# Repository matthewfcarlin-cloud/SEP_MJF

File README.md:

# RECO

**A smart tape and app that helps people recovering from an injury get back to their lives sooner, with fewer setbacks. It tracks the injured joint every day, shows their progress and what comes before their pain, and gives their PT the full picture between visits.**

A PT sees you for 1 to 3 hours a week. RECO covers the other 160+.

- **Track:** the tape records how the joint moves and how much it's used through daily life.
- **Log:** press the button on the device when something hurts.
- **Learn:** RECO finds what comes before your pain and learns your line.
- **Adapt:** your progress, plan and warnings update from what you actually did.
- **Share:** your PT gets a data-driven report before each appointment.

The vision covers knee, shoulder and elbow injuries, with or without a PT. The first version starts with the knee. RECO was first called Kinn, so the code still lives under `kinn/`.

## Start here

- **Vision:** [`kinn/docs/vision.md`](kinn/docs/vision.md) is the source of truth for what RECO is, who it's for, and what's still open.
- **Decisions:** [`kinn/docs/decisions.md`](kinn/docs/decisions.md) is the running log of what was decided and why.
- **History:** [`kinn/CONTEXT.md`](kinn/CONTEXT.md) covers how the product got here, along with brand, site and market notes.

## In this repo

- **App:** [`kinn/app/`](kinn/app/) is the Expo app and the `@reco/core` logic package. Details are in [`feature-spec.md`](kinn/docs/feature-spec.md) (written before the current vision), [`architecture.md`](kinn/docs/architecture.md), [`scoring-methods.md`](kinn/docs/scoring-methods.md) and [`backend.md`](kinn/docs/backend.md).
- **Hardware:** [`kinn/firmware/`](kinn/firmware/) and [`kinn/hardware/`](kinn/hardware/) hold the prototype tape firmware and coin PCB. [`kinn/cad/`](kinn/cad/) holds the CAD.
- **Website and waitlist:** [`kinn/site/`](kinn/site/) is the static site and a small Express API, deployed on Vercel. Setup is in its README.
- **Renders and video:** [`kinn/renders/`](kinn/renders/), [`kinn/video/`](kinn/video/) and the scene scripts in [`kinn/blender/`](kinn/blender/).
- **Archive:** [`kinn/archive/`](kinn/archive/) holds earlier concepts and demos, including the Poise posture strip and the hackathon learning demo.

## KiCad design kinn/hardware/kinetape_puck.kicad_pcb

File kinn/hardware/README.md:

# KineTape puck — PCB (rev A)

A 25.4 mm (1 in) round, 4-layer board that snaps onto the tape: ESP32 + printed BLE antenna,
capacitive touch button, status LED, and four spring contacts on the bottom that reach the battery
and pressure sensor built into the tape.

| | |
|---|---|
|  |  |

**Status:** schematic ERC-clean; board fully routed, **0 DRC violations / 0 unconnected / 0 schematic-parity
errors** (KiCad 10.0.7, all severities). **Not yet fabricated or RF-tested** — see [Before you order](#before-you-order).

## What's on it

| Block | Parts | Notes |
|---|---|---|
| MCU | U1 ESP32-PICO-V3-02 (LGA-48, 7×7 mm) | Classic ESP32 + 8 MB flash + 2 MB PSRAM + crystal in one package, so the existing `esp32dev` firmware runs. |
| Antenna | AE1 printed inverted-F, R10 + C11/C12 pi network | IFA runs along the top edge (above the ground cut). C11/C12 are **DNP** until tuned. |
| Power | Q1 AO3401A, U2 ME6211 3.3 V LDO, C1/C3 | Battery comes from the tape (J1). Q1 = reverse-polarity protection. ME6211: 500 mA, VIN up to 6 V. |
| Battery sense | R1/R2 1 MΩ divider + C4 → GPIO35 | VBAT/2, ~2 µA drain. |
| Sensor | J3/J4 + R7, R8, R9, C10 | Same divider as the firmware README: 3V3 → sensor → GPIO34 with 10 kΩ to GND (+1 kΩ/100 nF RC filter). |
| Touch | TS1 Ø6.5 mm electrode, R6 470 Ω | Electrode on the top layer under solder mask; no copper under it on inner/bottom layers. |
| LED | LED1 green 0603, R5 470 Ω → GPIO2 | Same pin as the firmware. |
| ESD | D1–D3 (0402) on every tape contact | The contacts touch the tape and skin. |

### Tape contacts (bottom side, Harwin P70-1000045R SMT spring pins)

| Contact | Net | Position (from centre, top view) |
|---|---|---|
| J1 | VBAT in (3.0–5.5 V) | (+8.8, +1.5) mm |
| J2 | GND | (+6.5, −7.2) mm |
| J3 | SENS_A (3.3 V via 100 Ω) | (−8.8, +1.5) mm |
| J4 | SENS_B (→ ADC) | (−6.5, −7.2) mm |

The pattern is deliberately asymmetric, so the puck can only mate one way. The tape needs four flat
conductive pads (snaps, conductive fabric or foil) at these positions. Spring free height is 3.5 mm,
working height 2.9 mm.

### GPIO map (firmware)

| GPIO | Function | vs current firmware |
|---|---|---|
| 34 | Sensor ADC (ADC1_CH6) | unchanged |
| 2 | Status LED | unchanged |
| 35 | Battery sense, VBAT/2 (ADC1_CH7) | new; matches the "Future" note in `firmware/README.md` |
| 13 | Touch button (`T4`, `touchRead(13)`) | new |
| 1 / 3 | UART0 TX / RX (programming pads) | unchanged |
| 0 / EN | Boot / reset (programming pads) | — |

### Programming

The 2×3 pad grid on the bottom (Ø1.0 mm, 2.0 mm pitch) is for a pogo-pin jig plus a 3.3 V USB-UART adapter:

```
TP3 TXD  (4.5,-1.0)   TP4 RXD (6.5,-1.0)   TP1 3V3 (8.5,-1.0)
TP5 EN   (4.5,-3.0)   TP6 IO0 (6.5,-3.0)   TP2 GND (8.5,-3.0)
```

There is no auto-reset circuit. To enter the bootloader, hold IO0 to GND and pulse EN to GND, then flash
with `pio run -t upload`. To power the board for flashing, feed VBAT through J1. Back-feeding TP1 (3V3)
works but pushes current into the LDO output.

## Board

- 25.4 mm circle, **4 layers, 1.0 mm** FR-4. F.Cu signals + GND pour; In1 = solid GND plane;
  In2 = +3V3 plane; B.Cu signals + GND pour.
- Rules: 0.15 mm track/space (power 0.25–0.3 mm), vias 0.5/0.3 mm (thermal-pad vias 0.5/0.25 mm),
  all within JLCPCB's standard 4-layer capability.
- RF feed: 0.2 mm trace, pre-routed and locked; ground stitching along the antenna ground edge.
- No copper on any layer above the ground edge (antenna keepout), and none under the touch electrode on the
  inner and bottom layers.

## Before you order

These are the things I could not verify from here. Each one should be checked rather than assumed.

1. **The antenna is untuned and uncertified.** The IFA (19.9 mm arm + stub) is deliberately a bit long,
   so it should resonate low. Plan on a VNA (a NanoVNA is enough): measure S11 at R10, trim the open end
   of the arm, and fit C11/C12 to match 50 Ω. The enclosure and skin will detune it further, so tune it
   inside the enclosure, on an arm. Without tuning, BLE will probably still work at a few metres, but range
   is unknown. A bare chip with your own antenna also means the radio is uncertified (FCC/CE), which is fine
   for a prototype but not for selling it.
2. **ESP32 land pattern.** The LGA-48 footprint is built from Espressif's datasheet (v1.4, Fig. 16:
   0.25 × 0.68 mm lands, 6.73 mm between opposite land centres, 4.5 mm thermal pad with a 4.0 mm
   mask opening). Compare it against Espressif's land-pattern source file before ordering.
3. **Spring-contact pad.** Ø2.4 mm pad for the Ø2.0 mm Harwin P70-1000045R body. Check it against
   Harwin's drawing.
4. **JLCPCB part numbers.** Check stock and Basic/Extended status in the BOM upload. The ESP32
   (C908392), ESD diodes and springs are Extended parts, so each adds a loading fee.
5. **Rotations.** In JLCPCB's placement preview, check pin 1 of U1, the orientation of U2/Q1, and LED1
   polarity.
6. **Double-sided assembly.** J1–J4 are on the bottom. Either pay for both sides, or assemble the top
   only and hand-solder the four springs.
7. **Battery and power budget.** BLE on a classic ESP32 averages roughly 40–100 mA, with peaks around
   130–250 mA. The battery in the tape has to deliver those peaks through the contacts, so contact
   resistance matters. Firmware sleep (see the power notes in `firmware/README.md`) decides battery life
   far more than this board does.

## Regenerating

Everything is generated from [`scripts/design.py`](scripts/design.py) (parts, nets, placement).
Don't hand-edit the `.kicad_*` files and then rerun the scripts, because the scripts overwrite them.
Run with KiCad's Python from `hardware/`:

```bash
"C:/Program Files/KiCad/10.0/bin/python.exe" scripts/build.py    # footprints, schematic, placed board, fanout
"C:/Program Files/KiCad/10.0/bin/python.exe" scripts/route.py    # Freerouting + finishing router + stitching
"C:/Program Files/KiCad/10.0/bin/python.exe" scripts/export.py   # DRC gate, then fab/ outputs
```

`route.py` needs `tools/freerouting.jar` (Freerouting 1.9.0, Java 17; git-ignored). It briefly opens a
Freerouting window. Whatever Freerouting leaves unrouted, the grid router in `scripts/finish.py`
completes. `export.py` refuses to write outputs unless DRC and schematic parity are clean.

| Script | Does |
|---|---|
| `design.py` | The circuit: every part, its LCSC number, pin → net, PCB position |
| `footprints.py` | Custom footprints: ESP32-PICO LGA-48, IFA antenna, touch pad, spring contact |
| `schematic.py` | Writes the `.kicad_sch` (net labels on every pin); KiCad's own netlist export is then checked against `design.py` |
| `build.py` | Board outline, placement, pours, keepouts, locked RF route, power fanout and escape vias |
| `fanout.py` / `finish.py` | Clearance-checked via fanout; grid A* router for leftovers |
| `export.py` | Gerbers + drill zip, JLCPCB BOM/CPL, schematic PDF, STEP |

## Ordering (JLCPCB)

1. Upload `fab/kinetape_puck_gerbers.zip`. Set 4 layers, 1.0 mm, ENIG (recommended for the LGA and the
   spring contacts), and the default impedance-free stackup.
2. PCB Assembly: upload `fab/kinetape_puck_bom.csv` and `fab/kinetape_puck_cpl.csv`, then check the
   placement preview (see item 5 above).
3. Optional: use `fab/kinetape_puck.step` to design the enclosure. It has the antenna at the top edge,
   and the touch electrode should sit under a thin (≤ 1.5 mm) plastic lid.

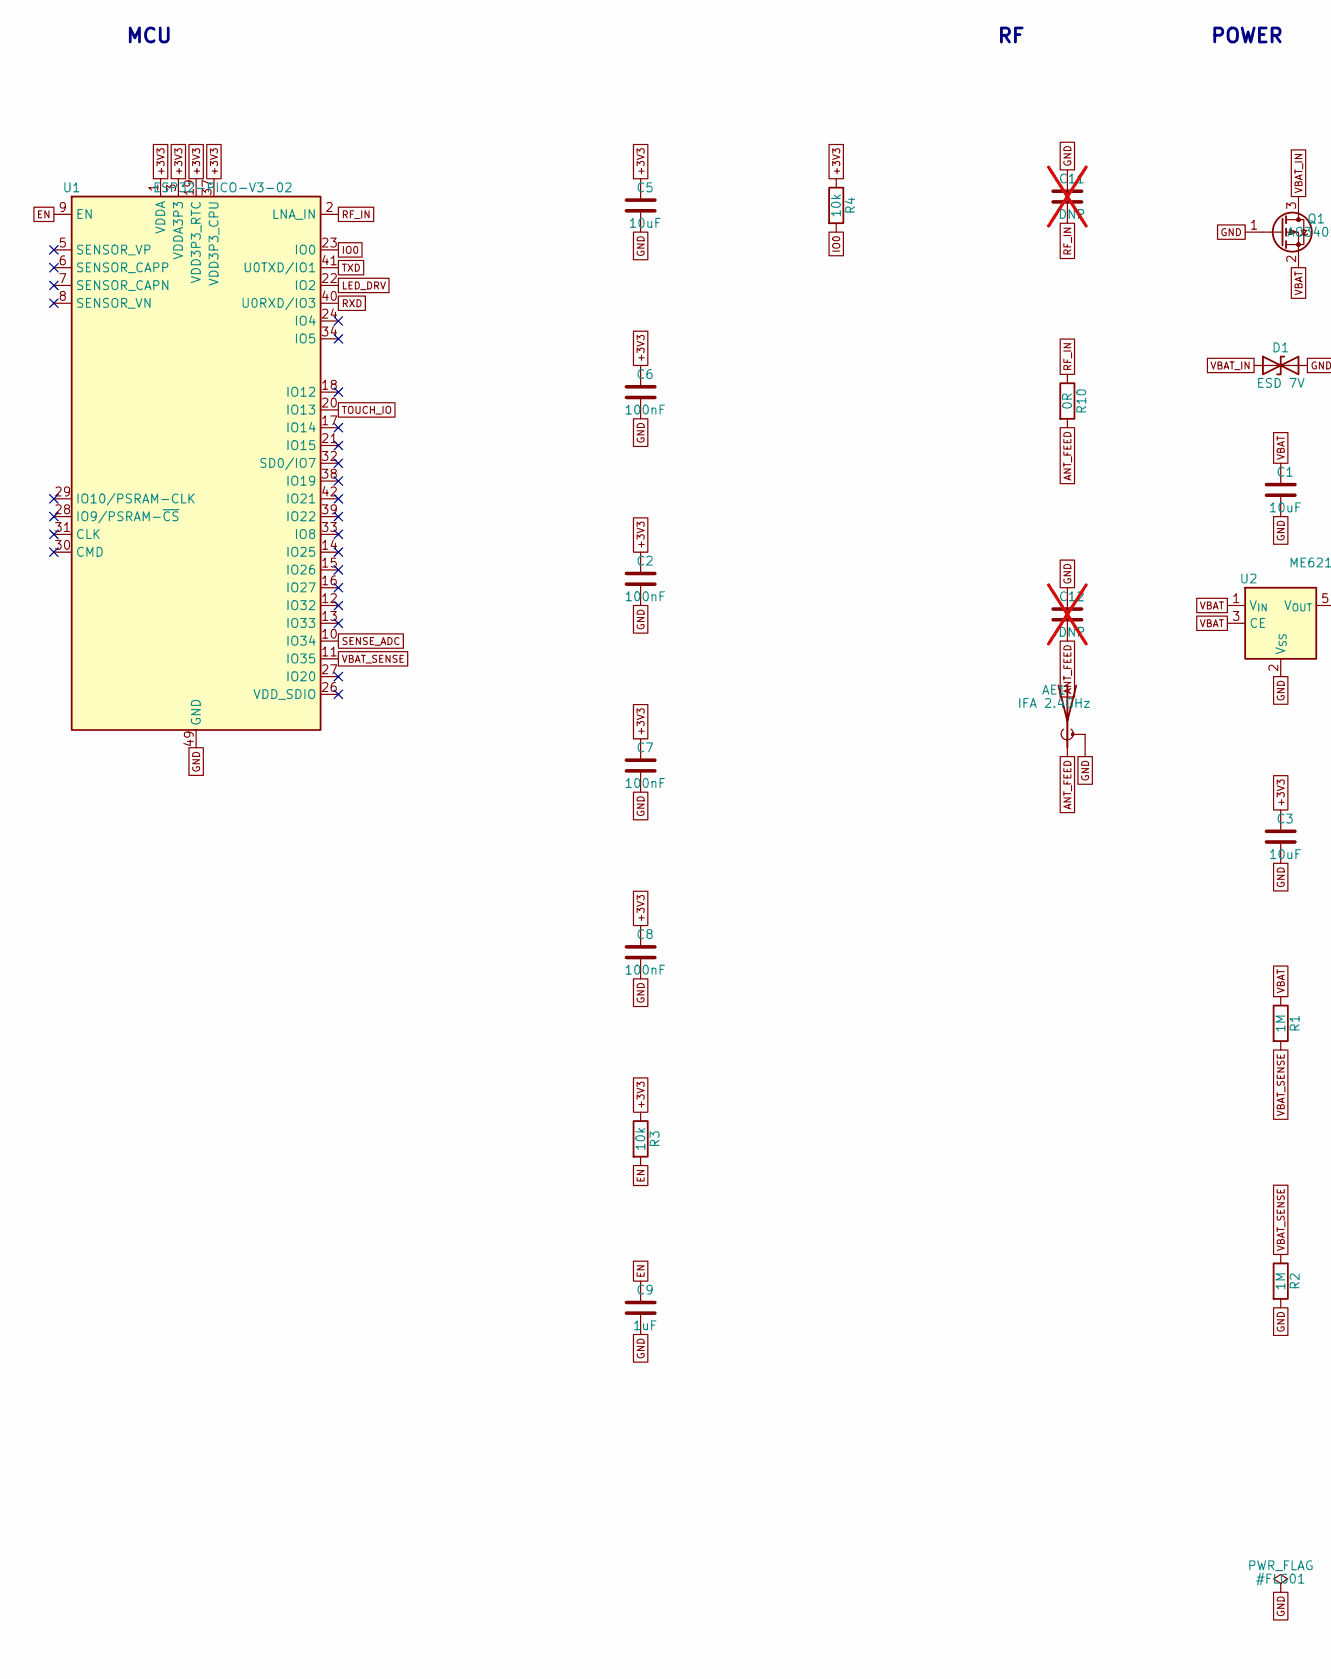
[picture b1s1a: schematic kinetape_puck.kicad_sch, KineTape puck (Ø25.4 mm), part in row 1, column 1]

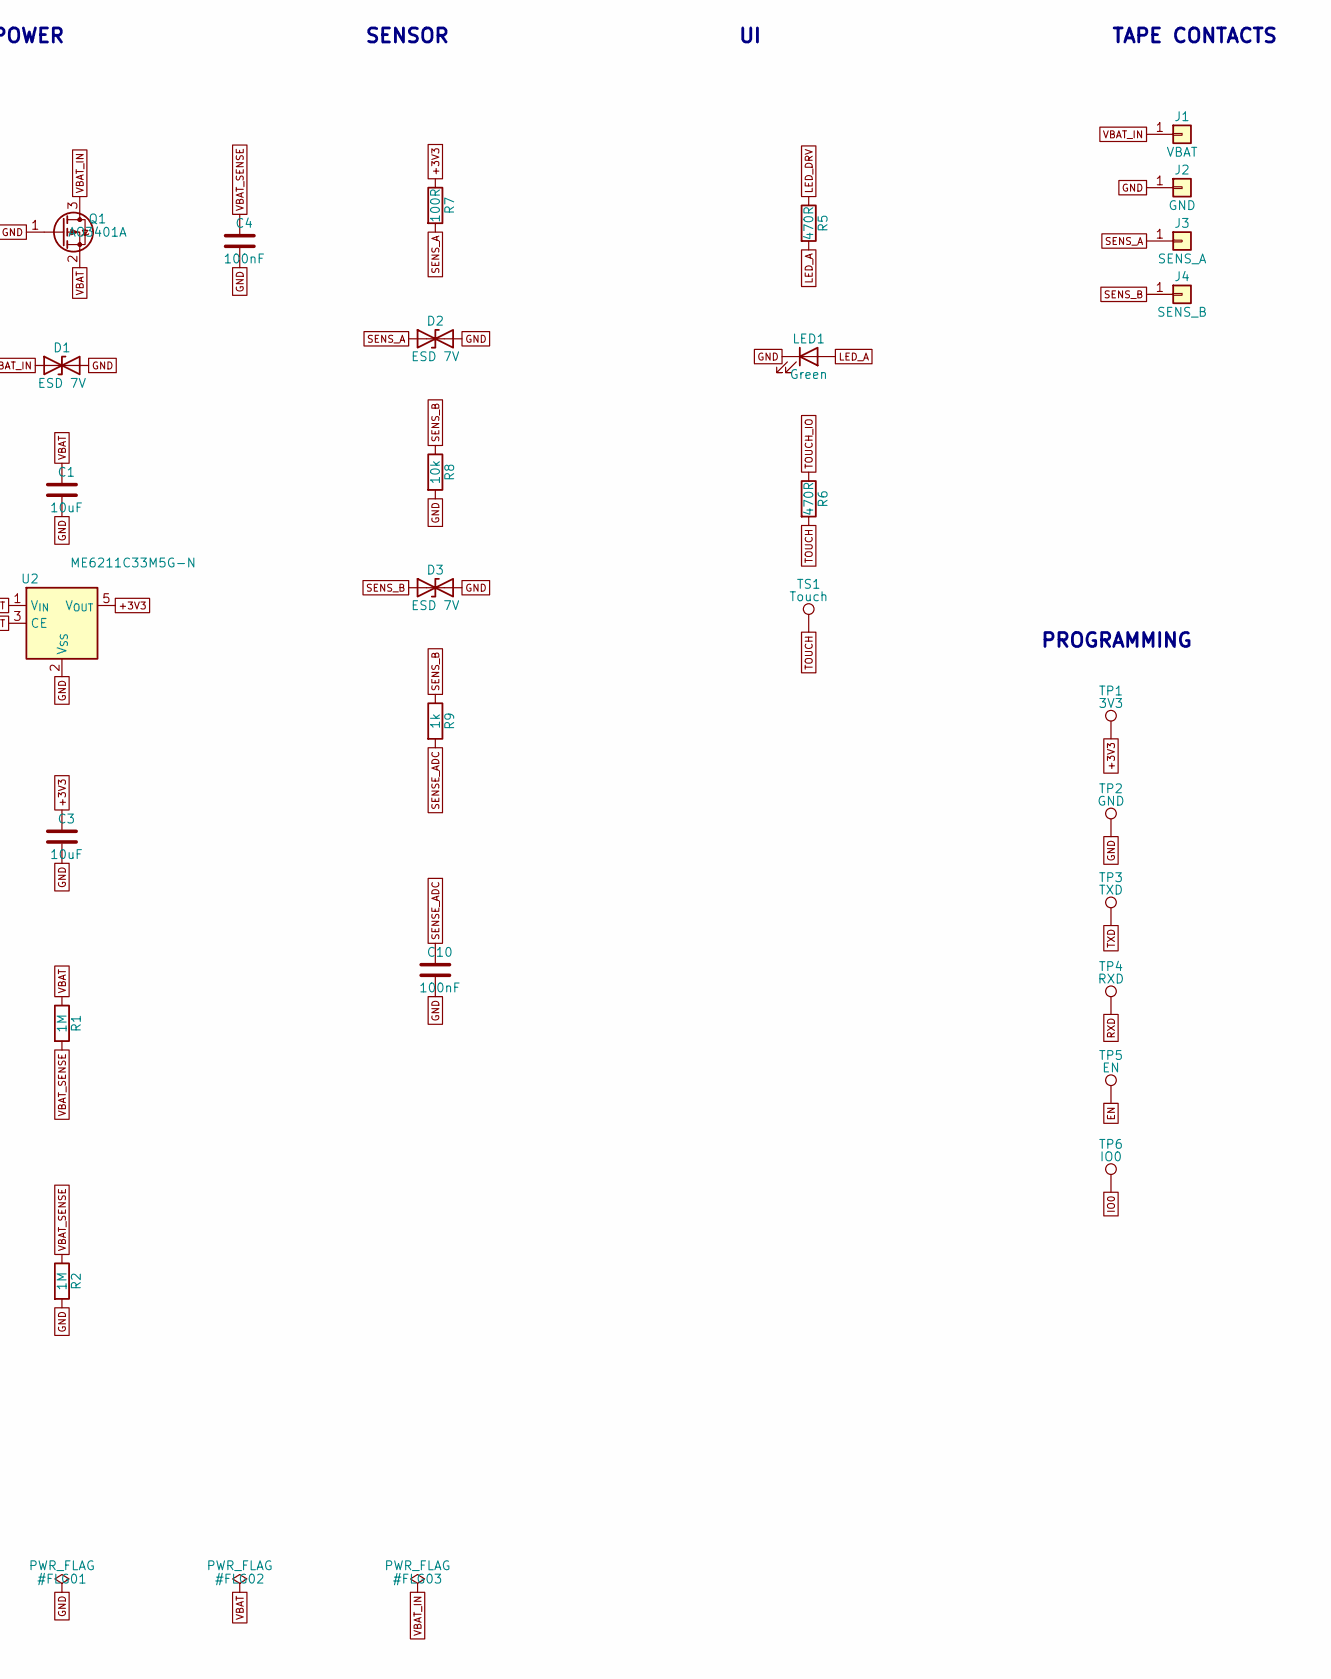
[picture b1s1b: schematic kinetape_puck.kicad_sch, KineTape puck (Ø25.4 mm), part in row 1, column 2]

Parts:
AE1: IFA 2.4GHz; Antenna_IFA_2G4_Puck
C1, C3, C5: 10uF; C_0402_1005Metric; LCSC C15525
C2, C4, C6, C7, C8, C10: 100nF; C_0402_1005Metric; LCSC C1525
C9: 1uF; C_0402_1005Metric; LCSC C52923
C11, C12: DNP; C_0402_1005Metric; not fitted
D1, D2, D3: ESD 7V; D_0402_1005Metric; LCSC C2763588
J1: VBAT; SpringContact_Harwin_P70-1000045R; LCSC C17702549
J2: GND; SpringContact_Harwin_P70-1000045R; LCSC C17702549
J3: SENS_A; SpringContact_Harwin_P70-1000045R; LCSC C17702549
J4: SENS_B; SpringContact_Harwin_P70-1000045R; LCSC C17702549
LED1: Green; LED_0603_1608Metric; LCSC C72043
Q1: AO3401A; SOT-23; LCSC C15127
R1, R2: 1M; R_0402_1005Metric; LCSC C26083
R3, R4, R8: 10k; R_0402_1005Metric; LCSC C25744
R5, R6: 470R; R_0402_1005Metric; LCSC C25117
R7: 100R; R_0402_1005Metric; LCSC C25076
R9: 1k; R_0402_1005Metric; LCSC C11702
R10: 0R; R_0402_1005Metric; LCSC C17168
TP1: 3V3; TestPoint_Pad_D1.0mm
TP2: GND; TestPoint_Pad_D1.0mm
TP3: TXD; TestPoint_Pad_D1.0mm
TP4: RXD; TestPoint_Pad_D1.0mm
TP5: EN; TestPoint_Pad_D1.0mm
TP6: IO0; TestPoint_Pad_D1.0mm
TS1: Touch; TouchPad_D6.5mm
U1: ESP32-PICO-V3-02; ESP32-PICO-V3-02_LGA48_7x7mm; LCSC C908392
U2: ME6211C33M5G-N; SOT-23-5; LCSC C82942

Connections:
+3V3: C2.1, C3.1, C5.1, C6.1, C7.1, C8.1, R3.1, R4.1, R7.1, TP1.1, U1.1 (VDDA), U1.3 (VDDA3P3), U1.4 (VDDA3P3), U1.19 (VDD3P3_RTC), U1.37 (VDD3P3_CPU), U1.43 (VDDA), U1.46 (VDDA), U2.5 (V_{OUT})
ANT_FEED: AE1.1 (A), C12.2, R10.2
EN: C9.1, R3.2, TP5.1, U1.9 (EN)
GND: AE1.2 (Shield), C1.2, C2.2, C3.2, C4.2, C5.2, C6.2, C7.2, C8.2, C9.2, C10.2, C11.1, C12.1, D1.2 (A2), D2.2 (A2), D3.2 (A2), J2.1, LED1.1 (K), Q1.1 (G), R2.2, R8.2, TP2.1, U1.49 (GND), U2.2 (V_{SS})
IO0: R4.2, TP6.1, U1.23 (IO0)
LED_A: LED1.2 (A), R5.2
LED_DRV: R5.1, U1.22 (IO2)
RF_IN: C11.2, R10.1, U1.2 (LNA_IN)
RXD: TP4.1, U1.40 (U0RXD/IO3)
SENSE_ADC: C10.1, R9.2, U1.10 (IO34)
SENS_A: D2.1 (A1), J3.1, R7.2
SENS_B: D3.1 (A1), J4.1, R8.1, R9.1
TOUCH: R6.2, TS1.1
TOUCH_IO: R6.1, U1.20 (IO13)
TXD: TP3.1, U1.41 (U0TXD/IO1)
VBAT: C1.1, Q1.2 (S), R1.1, U2.1 (V_{IN}), U2.3 (CE)
VBAT_IN: D1.1 (A1), J1.1, Q1.3 (D)
VBAT_SENSE: C4.1, R1.2, R2.1, U1.11 (IO35)

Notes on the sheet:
MCU
POWER
SENSOR
TAPE CONTACTS
PROGRAMMING

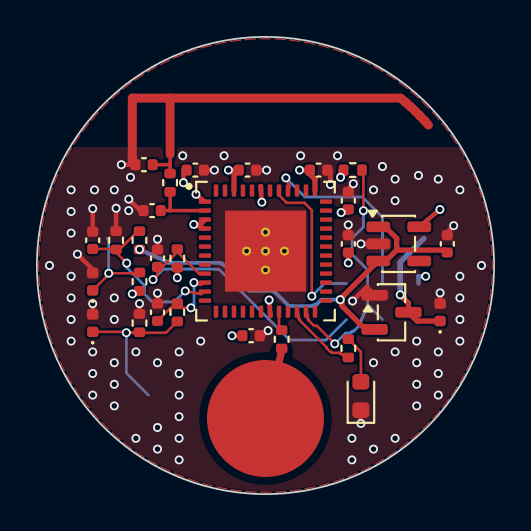
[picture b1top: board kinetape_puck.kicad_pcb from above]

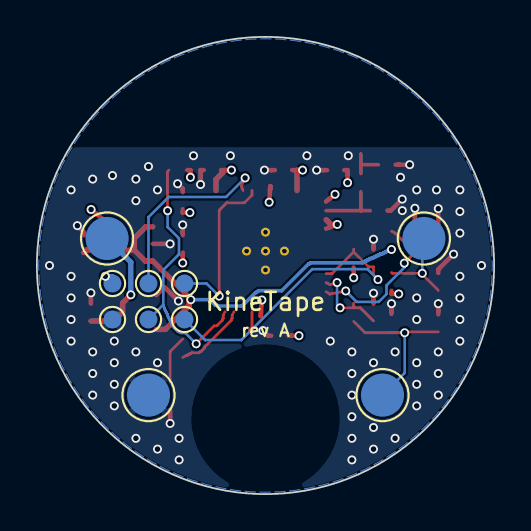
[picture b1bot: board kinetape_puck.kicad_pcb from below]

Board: 4 copper layers, 25.4 x 25.4 mm, 41 parts (10 on the bottom side), 18 nets.

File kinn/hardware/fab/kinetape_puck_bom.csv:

Comment,Designator,Footprint,LCSC Part #
10uF,"C1,C3,C5",C_0402_1005Metric,C15525
100nF,"C2,C4,C6,C7,C8,C10",C_0402_1005Metric,C1525
1uF,C9,C_0402_1005Metric,C52923
ESD 7V,"D1,D2,D3",D_0402_1005Metric,C2763588
P70-1000045R,"J1,J2,J3,J4",SpringContact_Harwin_P70-1000045R,C17702549
Green,LED1,LED_0603_1608Metric,C72043
AO3401A,Q1,SOT-23,C15127
1M,"R1,R2",R_0402_1005Metric,C26083
0R,R10,R_0402_1005Metric,C17168
10k,"R3,R4,R8",R_0402_1005Metric,C25744
470R,"R5,R6",R_0402_1005Metric,C25117
100R,R7,R_0402_1005Metric,C25076
1k,R9,R_0402_1005Metric,C11702
ESP32-PICO-V3-02,U1,ESP32-PICO-V3-02_LGA48_7x7mm,C908392
ME6211C33M5G-N,U2,SOT-23-5,C82942

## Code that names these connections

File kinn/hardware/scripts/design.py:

"""KineTape puck: single source of truth for the circuit and placement.

Coordinates for PCB placement are in mm, math orientation (+y up), relative to
the board centre. Board is a 25.4 mm (1 in) circle.
"""

BOARD_R = 12.7
GROUND_EDGE_Y = 6.5          # ground stops here; antenna lives above it
PROJECT = "kinetape_puck"

# LCSC numbers (verify in the JLCPCB BOM tool before ordering)
LCSC = {
    "R10k": "C25744", "R1k": "C11702", "R100": "C25076", "R470": "C25117",
    "R1M": "C26083", "R0": "C17168", "C100n": "C1525", "C1u": "C52923",
    "C10u": "C15525", "LED": "C72043", "LDO": "C82942", "PFET": "C15127",
    "ESD": "C2763588", "PICO": "C908392", "SPRING": "C17702549",
}

R0402 = "Resistor_SMD:R_0402_1005Metric"
C0402 = "Capacitor_SMD:C_0402_1005Metric"


def R(ref, val, lcsc, a, b, pos, rot=0, group="", dnp=False):
    return dict(ref=ref, lib="Device:R", value=val, fp=R0402, lcsc=lcsc,
                pins={"1": a, "2": b}, pos=pos, rot=rot, group=group, dnp=dnp)


def C(ref, val, lcsc, a, b, pos, rot=0, group="", dnp=False):
    return dict(ref=ref, lib="Device:C", value=val, fp=C0402, lcsc=lcsc,
                pins={"1": a, "2": b}, pos=pos, rot=rot, group=group, dnp=dnp)


# ESP32-PICO-V3-02 pin -> net (unlisted pins are left unconnected / NC)
U1_PINS = {
    "1": "+3V3", "2": "RF_IN", "3": "+3V3", "4": "+3V3",
    "9": "EN", "10": "SENSE_ADC", "11": "VBAT_SENSE",
    "19": "+3V3", "20": "TOUCH_IO", "22": "LED_DRV", "23": "IO0",
    "37": "+3V3", "40": "RXD", "41": "TXD", "43": "+3V3", "46": "+3V3",
    "49": "GND",
}

PARTS = [
    # ---- MCU -------------------------------------------------------------
    dict(ref="U1", lib="MCU_Espressif:ESP32-PICO-V3-02", value="ESP32-PICO-V3-02",
         fp="KineTape:ESP32-PICO-V3-02_LGA48_7x7mm", lcsc=LCSC["PICO"],
         pins=U1_PINS, pos=(0, 0.8), rot=0, group="MCU"),
    C("C5", "10uF", LCSC["C10u"], "+3V3", "GND", (4.6, 3.6), 90, "MCU"),
    C("C6", "100nF", LCSC["C100n"], "+3V3", "GND", (-3.9, 5.3), 0, "MCU"),
    C("C2", "100nF", LCSC["C100n"], "+3V3", "GND", (-1.0, 5.3), 0, "MCU"),
    C("C7", "100nF", LCSC["C100n"], "+3V3", "GND", (2.95, 5.3), 0, "MCU"),
    C("C8", "100nF", LCSC["C100n"], "+3V3", "GND", (-0.8, -3.9), 0, "MCU"),
    R("R3", "10k", LCSC["R10k"], "+3V3", "EN", (-4.9, 0.4), 90, "MCU"),
    C("C9", "1uF", LCSC["C1u"], "EN", "GND", (-6.0, 0.4), 90, "MCU"),
    R("R4", "10k", LCSC["R10k"], "+3V3", "IO0", (4.85, 5.3), 0, "MCU"),

    # ---- RF: pi network (C11/C12 DNP until tuned with a VNA) + printed IFA --
    C("C11", "DNP", "", "GND", "RF_IN", (-6.3, 3.05), 0, "RF", dnp=True),
    R("R10", "0R", LCSC["R0"], "RF_IN", "ANT_FEED", (-5.3, 4.6), 90, "RF"),
    C("C12", "DNP", "", "GND", "ANT_FEED", (-6.75, 5.6), 0, "RF", dnp=True),
    dict(ref="AE1", lib="Device:Antenna_Shield", value="IFA 2.4GHz",
         fp="KineTape:Antenna_IFA_2G4_Puck", lcsc="", pins={"1": "ANT_FEED", "2": "GND"},
         pos=(0, 0), rot=0, group="RF", bom=False),

    # ---- Power: battery from tape -> reverse protection -> LDO ------------
    dict(ref="Q1", lib="Transistor_FET:AO3401A", value="AO3401A",
         fp="Package_TO_SOT_SMD:SOT-23", lcsc=LCSC["PFET"],
         pins={"1": "GND", "2": "VBAT", "3": "VBAT_IN"}, pos=(7.0, -2.6), rot=0, group="Power"),
    dict(ref="D1", lib="Device:D_TVS", value="ESD 7V", fp="Diode_SMD:D_0402_1005Metric",
         lcsc=LCSC["ESD"], pins={"1": "VBAT_IN", "2": "GND"}, pos=(9.7, -2.6), rot=90, group="Power"),
    C("C1", "10uF", LCSC["C10u"], "VBAT", "GND", (10.1, 1.2), 90, "Power"),
    dict(ref="U2", lib="Regulator_Linear:ME6211C33M5", value="ME6211C33M5G-N",
         fp="Package_TO_SOT_SMD:SOT-23-5", lcsc=LCSC["LDO"],
         pins={"1": "VBAT", "2": "GND", "3": "VBAT", "5": "+3V3"}, pos=(7.4, 1.2), rot=0, group="Power"),
    C("C3", "10uF", LCSC["C10u"], "+3V3", "GND", (4.6, 1.2), 90, "Power"),
    R("R1", "1M", LCSC["R1M"], "VBAT", "VBAT_SENSE", (-7.0, 1.4), 90, "Power"),
    R("R2", "1M", LCSC["R1M"], "VBAT_SENSE", "GND", (-8.3, 1.4), 90, "Power"),
    C("C4", "100nF", LCSC["C100n"], "VBAT_SENSE", "GND", (-9.6, 1.4), 90, "Power"),

    # ---- Sensor interface (thin-film FSR in the tape) ---------------------
    R("R7", "100R", LCSC["R100"], "+3V3", "SENS_A", (-7.0, -0.9), 90, "Sensor"),
    dict(ref="D2", lib="Device:D_TVS", value="ESD 7V", fp="Diode_SMD:D_0402_1005Metric",
         lcsc=LCSC["ESD"], pins={"1": "SENS_A", "2": "GND"}, pos=(-9.6, -0.9), rot=90, group="Sensor"),
    R("R8", "10k", LCSC["R10k"], "SENS_B", "GND", (-7.0, -3.2), 90, "Sensor"),
    dict(ref="D3", lib="Device:D_TVS", value="ESD 7V", fp="Diode_SMD:D_0402_1005Metric",
         lcsc=LCSC["ESD"], pins={"1": "SENS_B", "2": "GND"}, pos=(-9.6, -3.2), rot=90, group="Sensor"),
    R("R9", "1k", LCSC["R1k"], "SENS_B", "SENSE_ADC", (-4.9, -2.6), 90, "Sensor"),
    C("C10", "100nF", LCSC["C100n"], "SENSE_ADC", "GND", (-6.0, -2.6), 90, "Sensor"),

    # ---- UI: status LED + capacitive touch pad ----------------------------
    R("R5", "470R", LCSC["R470"], "LED_DRV", "LED_A", (4.6, -4.6), 90, "UI"),
    dict(ref="LED1", lib="Device:LED", value="Green", fp="LED_SMD:LED_0603_1608Metric",
         lcsc=LCSC["LED"], pins={"1": "GND", "2": "LED_A"}, pos=(5.3, -7.25), rot=90, group="UI"),
    R("R6", "470R", LCSC["R470"], "TOUCH_IO", "TOUCH", (0.9, -4.1), 270, "UI"),
    dict(ref="TS1", lib="Connector:TestPoint", value="Touch",
         fp="KineTape:TouchPad_D6.5mm", lcsc="", pins={"1": "TOUCH"},
         pos=(0, -8.5), rot=0, group="UI", bom=False),

    # ---- Bottom: spring contacts to the tape ------------------------------
    *[dict(ref=f"J{i}", lib="Connector_Generic:Conn_01x01", value=v,
           fp="KineTape:SpringContact_Harwin_P70-1000045R", lcsc=LCSC["SPRING"],
           pins={"1": n}, pos=p, rot=0, side="B", group="Tape contacts", bom_value="P70-1000045R")
      for i, (v, n, p) in enumerate([
          ("VBAT", "VBAT_IN", (8.8, 1.5)), ("GND", "GND", (6.5, -7.2)),
          ("SENS_A", "SENS_A", (-8.8, 1.5)), ("SENS_B", "SENS_B", (-6.5, -7.2))], 1)],

    # ---- Bottom: programming / debug test pads (pogo jig) -----------------
    *[dict(ref=f"TP{i}", lib="Connector:TestPoint", value=v,
           fp="TestPoint:TestPoint_Pad_D1.0mm", lcsc="", pins={"1": n}, pos=p,
           rot=0, side="B", group="Programming", bom=False)
      for i, (v, n, p) in enumerate([
          ("3V3", "+3V3", (8.5, -1.0)), ("GND", "GND", (8.5, -3.0)), ("TXD", "TXD", (4.5, -1.0)),
          ("RXD", "RXD", (6.5, -1.0)), ("EN", "EN", (4.5, -3.0)), ("IO0", "IO0", (6.5, -3.0))], 1)],
]

# Schematic-only power flags
PWR_FLAGS = ["GND", "VBAT", "VBAT_IN"]
